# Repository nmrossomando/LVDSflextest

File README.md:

# LVDSflextest
Test design for OSH Park's new flex PCB service.
And also a test design for some LVDS stuff.

I have designed for neither before. I'm sure it'll be fine.

For the flex pcb test, I was asked to:
- Have thin traces (check, 6 mil except for 3V3 and GND)
- Fill (check, ground planes on both layers)
- Tent vias (check)
- I quote, "Stitch the crap out of it" (check, double check, triple check)

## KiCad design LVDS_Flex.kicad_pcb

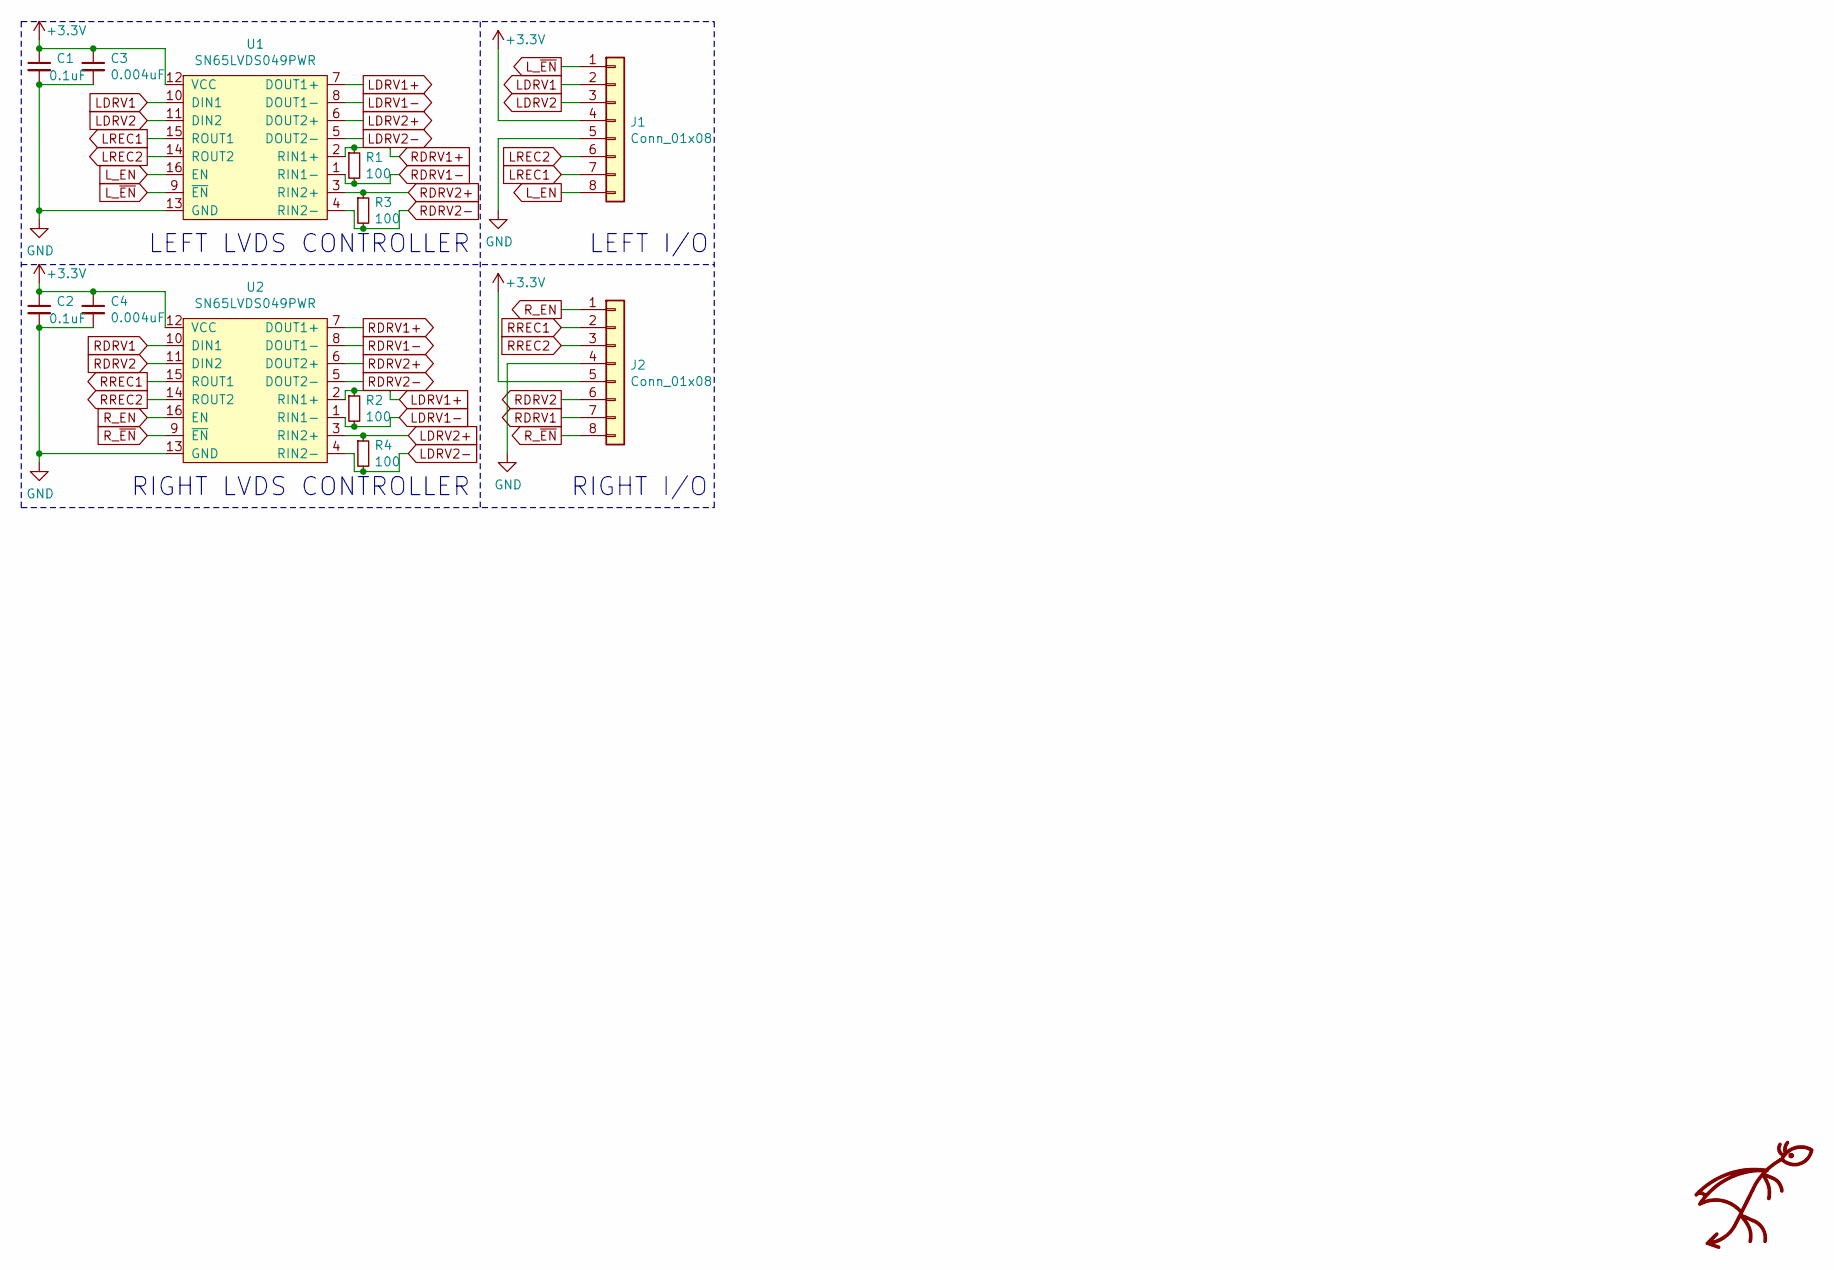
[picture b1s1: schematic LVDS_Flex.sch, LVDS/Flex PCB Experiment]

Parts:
C1, C2: 0.1uF; C_0402_1005Metric
C3, C4: 0.004uF; C_0402_1005Metric
J1, J2: Conn_01x08; PinHeader_1x08_P2.54mm_Vertical
R1, R2, R3, R4: 100; R_0402_1005Metric
U1, U2: SN65LVDS049PWR; TSSOP-16_4.4x5mm_P0.65mm

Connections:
+3V3: C1.1, C2.1, C3.1, C4.1, J1.4, J2.5, U1.12 (VCC), U2.12 (VCC)
GND: C1.2, C2.2, C3.2, C4.2, J1.5, J2.4, U1.13 (GND), U2.13 (GND)
LDRV1: J1.2, U1.10 (DIN1)
LDRV1+: R2.1, U1.7 (DOUT1+), U2.2 (RIN1+)
LDRV1-: R2.2, U1.8 (DOUT1-), U2.1 (RIN1-)
LDRV2: J1.3, U1.11 (DIN2)
LDRV2+: R4.1, U1.6 (DOUT2+), U2.3 (RIN2+)
LDRV2-: R4.2, U1.5 (DOUT2-), U2.4 (RIN2-)
LREC1: J1.7, U1.15 (ROUT1)
LREC2: J1.6, U1.14 (ROUT2)
L_EN: J1.8, U1.16 (EN)
L_~EN~: J1.1, U1.9 (~EN~)
RDRV1: J2.7, U2.10 (DIN1)
RDRV1+: R1.1, U1.2 (RIN1+), U2.7 (DOUT1+)
RDRV1-: R1.2, U1.1 (RIN1-), U2.8 (DOUT1-)
RDRV2: J2.6, U2.11 (DIN2)
RDRV2+: R3.1, U1.3 (RIN2+), U2.6 (DOUT2+)
RDRV2-: R3.2, U1.4 (RIN2-), U2.5 (DOUT2-)
RREC1: J2.2, U2.15 (ROUT1)
RREC2: J2.3, U2.14 (ROUT2)
R_EN: J2.1, U2.16 (EN)
R_~EN~: J2.8, U2.9 (~EN~)

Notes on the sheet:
LEFT LVDS CONTROLLER
RIGHT LVDS CONTROLLER
LEFT I/O
RIGHT I/O

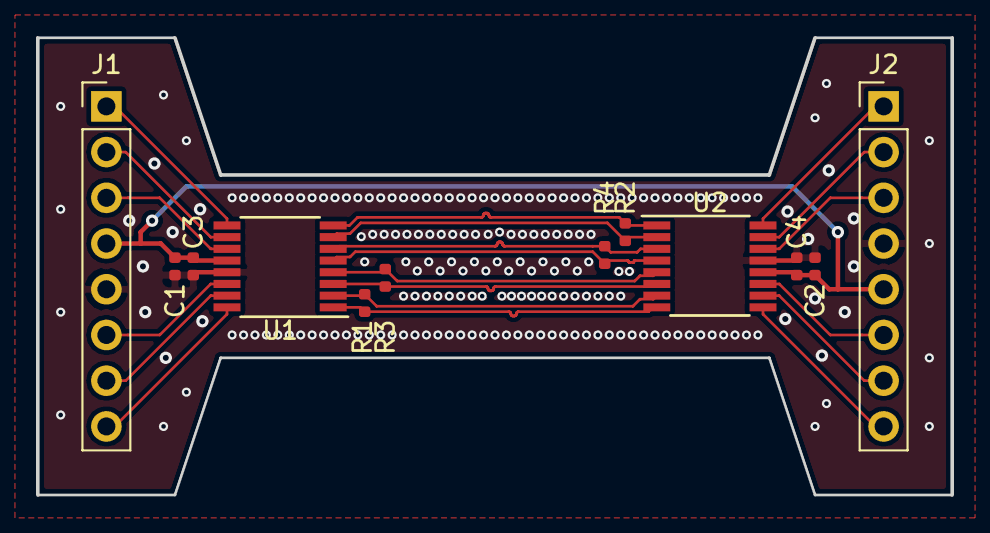
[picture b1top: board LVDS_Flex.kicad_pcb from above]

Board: 2 copper layers, 50.8 x 25.4 mm, 13 parts (1 on the bottom side), 22 nets.

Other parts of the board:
Ref**: Val**; DRAGON2

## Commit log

2019-02-19 License under public domain (WTFPL).
    I don't really care much about this little test board. So. WTFPL.
2019-02-19 Add gitignore with kicad template.
2019-02-19 Added readme.
2019-02-19 Removed files affected by gitignore.
